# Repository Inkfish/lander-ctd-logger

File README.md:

# CTD Logger for the Inkfish Open Oceans Landers

This repository holds firmware for the [SparkFun OpenLog][] specifically tailored to logging measurements from the [Sea-Bird SBE 49 FastCAT CTD][SBE 49] on the Inkfish Open Oceans landers.

  [SBE 49]: https://www.seabird.com/sbe-49-fastcat-ctd/product?id=60762467704
  [SparkFun OpenLog]: https://www.sparkfun.com/products/13712

The SBE 49 is capable of sampling at 16 Hz, but the lander controller functions best when it receives CTD data at 1 Hz. This firmware logs at the higher rate, then downsamples the data and passes it to the controller at the lower rate.

## Hardware

### Custom PCB

**(NEW):** The `hardware` directory contains KiCad designs for a printed circuit board that accepts a wider input voltage range and is designed to be significantly more resilient to power surges.

### Breadboard

The only components needed are the [SparkFun OpenLog][] and a [MAX3232 transceiver breakout][MAX3232].

(Note that some components are represented as SIP ICs for purposes of illustration. The leftmost pin of the MAX3232 transceiver above is `T1OUT`.)

In summary, the circuit interposes the communication between the CTD and Lander Control Board:

    +-------+          +---------------+         +-----------+
    | CTD   |          | MAX3232       |         | OpenLog   |
    |       |          |               |         |           |
    |   TX -------------> R1IN  R1OUT ------------> RX       |
    |       |  RS-232  |               |   TTL   |           |
    |       |    +------- T1OUT  T1IN <------------ TX       |
    |       |    |     |               |         |           |
    +-------+    |     +---------------+         +-----------+
                 |
                 |     +-------------------------------------+
                 |     | LCB                                 |
                 |     |                                     |
                 +------> CTD_RX                             |
                       |                                     |
                       +-------------------------------------+

**Note:** Consider the need to attach the programmer to the OpenLog. See Programming section below.

  [MAX3232]: https://www.sparkfun.com/products/11189

## Compiling

This project uses [PlatformIO][]. You can build the firmware and program the OpenLog using the PlatformIO Core CLI tool.

  [PlatformIO]: https://platformio.org/

First, clone the repository with submodules:

    git submodule update --init

Patch `SerialPort.h` to disable `BUFFERED_TX` and `ENABLE_RX_ERROR_CHECKING`:

    sed -i.bak \
      -e 's/\(#define BUFFERED_TX\) 1/\1 0/' \
      -e 's/\(#define ENABLE_RX_ERROR_CHECKING\) 1/\1 0/' \
      Libraries/SerialPort/SerialPort/SerialPort.h

Compile the project using PlatformIO to check for errors:

    pio run

## Programming

The OpenLog can be programmed using a 4-wire TTL UART to USB adapter. Review the [OpenLog Hookup Guide][hookup] for details on wiring. Importantly, the OpenLog `DTR` pin (inexplicably labeled `GRN`) must be connected to the programmer's `DTR` or `RTS` output.

  [hookup]: https://learn.sparkfun.com/tutorials/openlog-hookup-guide#hardware-hookup

    pio run -t upload

### Programming with a RS-232 cable

A USB to RS-232 cable (DB-9 connector) can also be used for programming. The `RX`/`TX` pinout on the DB-9 connector must be confirmed due to the various permutations.

  | DB-9              | MAX3232           | OpenLog |
  | ----------------- | ----------------- | ------- |
  | `TX` (pin 2 or 3) | `R1IN` → `R1OUT`  | `RX`    |
  | `RX` (pin 2 or 3) | `T1OUT` ← `T1IN`  | `TX`    |
  | `DTR` (pin 4)     | `R2IN`  → `R2OUT` | `GRN`   |
  | `GND` (pin 5)     | `GND`             | `GND`   |

### Programming with a Bus Pirate

The [Bus Pirate][] can be used as a programmer. Attach the pins as follows:

  | Bus Pirate | OpenLog |
  | ---------- | ------- |
  | `MOSI`     | `RX`    |
  | `MISO`     | `TX`    |
  | `CLK`      | `GRN`   | 
  | `GND`      | `GND`   |

Place the Bus Pirate into the transparent UART bridge mode with flow control signaling:

    # Enter UART mode, use baud 115200 for programming
    HiZ>m
    2. UART
    (1)>2
    ...

    # Enable power output on the pins
    UART>W
    POWER SUPPLIES ON
    Clutch engaged!!!

    # Start the transparent bridge
    UART>(3)
    UART bridge
    Reset to exit
    Are you sure? y

Disconnect the terminal session and proceed with programming the board.

  [Bus Pirate]: http://dangerousprototypes.com/docs/Bus_Pirate

## Configuration

By default, the OpenLog expects to receive and transmit data at 9600 baud, the same rate as the Lander Control Board. If this needs to be changed, a different baud rate can be written to the file `config.txt` at the root of the microSD card.

The SBE 49 must be configured for `OUTPUTFORMAT=3`, engineering units in decimal. 

## Testing

A quick and dirty test script can be used to send fake samples to the logger from a PC. The script counts the number of downsampled replies that match expected values.

    python3 test/simctd.py --sal --sv /dev/tty.usbserial

The `--sal` and `--sv` flags simulate the `OUTPUTSAL` (salinity) and `OUTPUTSV` (sound velocity) options on the SBE 49.

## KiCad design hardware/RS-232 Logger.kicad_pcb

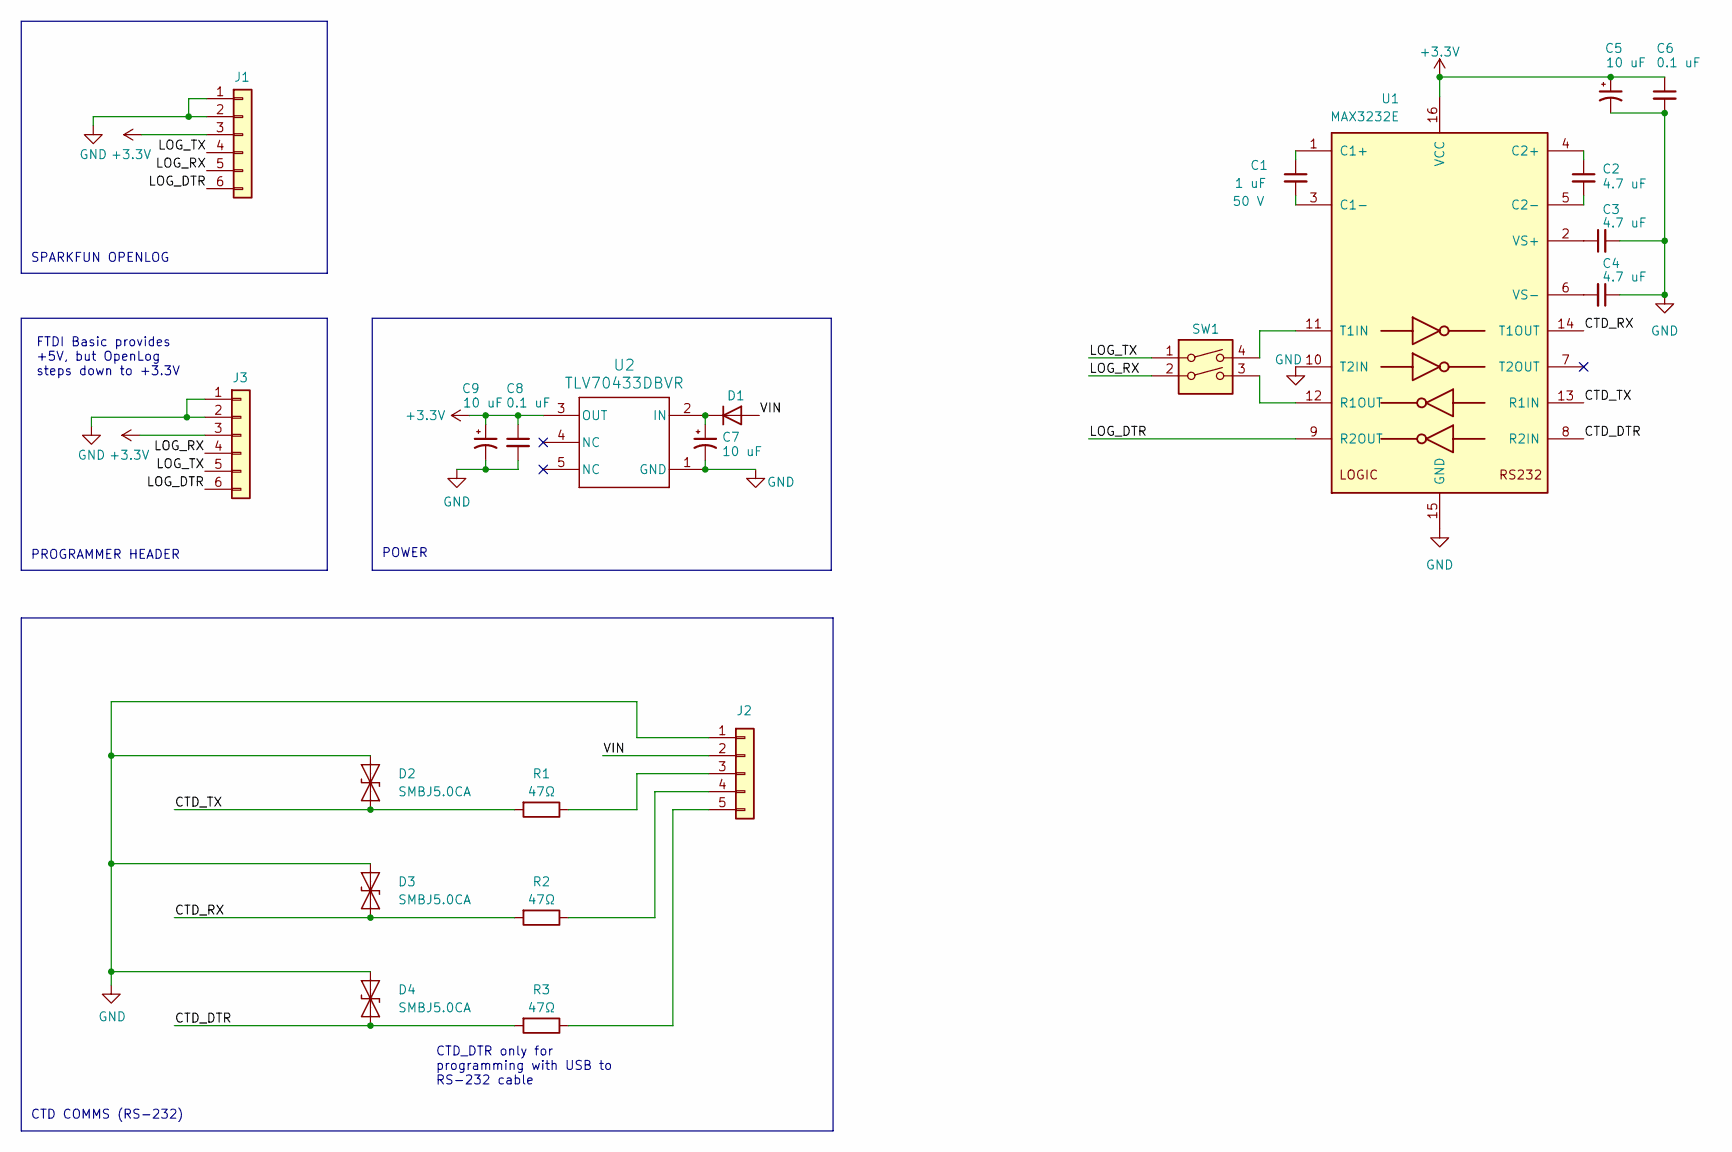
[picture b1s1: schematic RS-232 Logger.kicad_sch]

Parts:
C1: 1 uF; C_0805_2012Metric; Voltage 50 V; DigiKey CL21B105KBFNNNG
C2, C3, C4: 4.7 uF; C_0805_2012Metric; DigiKey CL21A475KBQNNNE
C5, C9: 10 uF; CAP_4 X 5.8_PAN; DigiKey EEE-FK1C100R
C6, C8: 0.1 uF; C_0805_2012Metric; DigiKey CL21B104KBCNNNC
C7: 10 uF; CAP_4 X 5.8_PAN
D1: D; DO-214BA_MCH
D2, D3, D4: SMBJ5.0CA; D_SMA
J1: Conn_01x06; PinSocket_1x06_P2.54mm_Vertical
J2: Conn_01x05; TerminalBlock_Phoenix_PT-1,5-5-3.5-H_1x05_P3.50mm_Horizontal
J3: Conn_01x06; PinHeader_1x06_P2.54mm_Vertical
R1, R2, R3: 47Ω; R_0603_1608Metric; DigiKey ESR03EZPJ470
SW1: SW_DIP_x02; SW_DIP_SPSTx02_Slide_6.7x6.64mm_W8.61mm_P2.54mm_LowProfile
U1: MAX3232E; 21-0056-E_90-0106-16L_MXM
U2: TLV70433DBVR; DBV0005A_N

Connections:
+3.3V: C5.1, C6.1, C8.1, C9.1, J1.3, J3.3, U1.16 (VCC), U2.3 (OUT)
/CTD_DTR: D4.2 (A2), R3.2, U1.8 (R2IN)
/CTD_RX: D3.2 (A2), R2.2, U1.14 (T1OUT)
/CTD_TX: D2.2 (A2), R1.2, U1.13 (R1IN)
/LOG_DTR: J1.6, J3.6, U1.9 (R2OUT)
/LOG_RX: J1.5, J3.4, SW1.2
/LOG_TX: J1.4, J3.5, SW1.1
/VIN: D1.2 (A), J2.2
GND: C3.2, C4.1, C5.2, C6.2, C7.2, C8.2, C9.2, D2.1 (A1), D3.1 (A1), D4.1 (A1), J1.1, J1.2, J2.1, J3.1, J3.2, U1.10 (T2IN), U1.15 (GND), U2.1 (GND)
unnamed: C7.1, D1.1 (K), U2.2 (IN)
unnamed: J2.3, R1.1
unnamed: J2.4, R2.1
unnamed: J2.5, R3.1
unnamed: C1.1, U1.1 (C1+)
unnamed: C1.2, U1.3 (C1-)
unnamed: C2.1, U1.4 (C2+)
unnamed: C2.2, U1.5 (C2-)
unnamed: SW1.3, U1.12 (R1OUT)
unnamed: SW1.4, U1.11 (T1IN)
unnamed: C3.1, U1.2 (VS+)
unnamed: C4.2, U1.6 (VS-)

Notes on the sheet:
CTD_DTR only for programming with USB to RS-232 cable
FTDI Basic provides +5V, but OpenLog steps down to +3.3V
CTD COMMS (RS-232)
SPARKFUN OPENLOG
POWER
PROGRAMMER HEADER

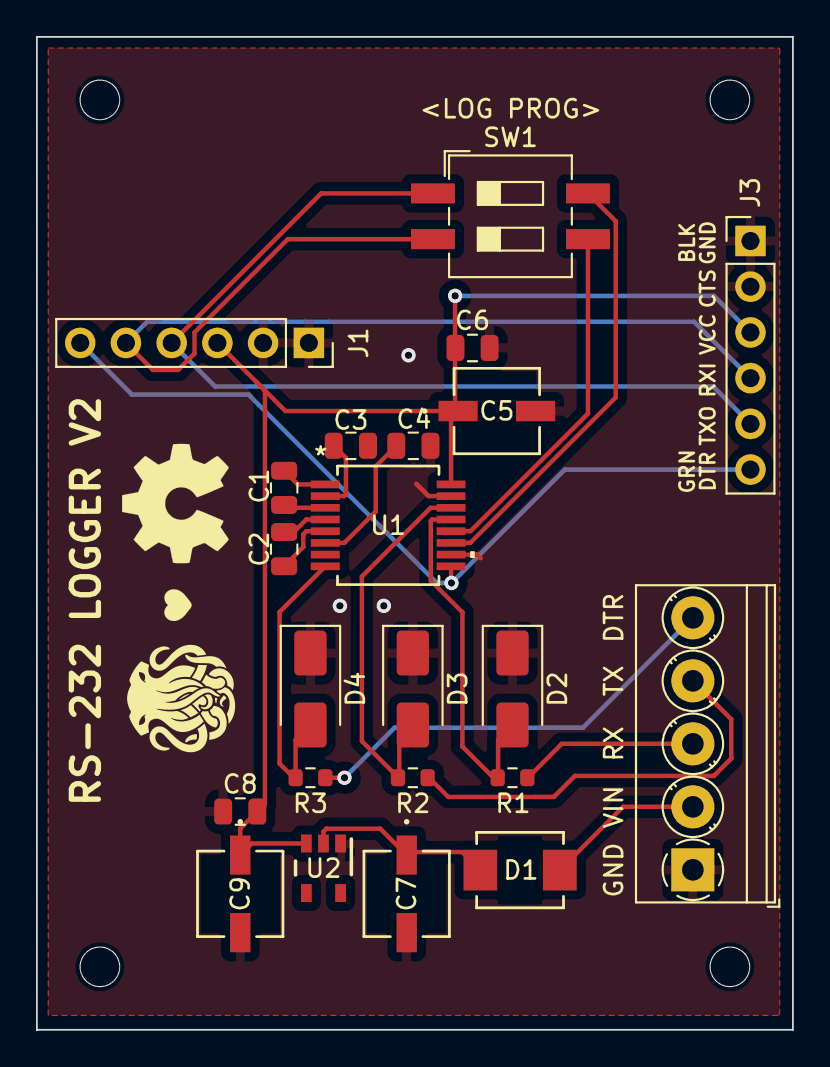
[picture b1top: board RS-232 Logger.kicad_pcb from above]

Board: 2 copper layers, 42.0 x 55.2 mm, 22 parts (0 on the bottom side), 21 nets.

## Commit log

2023-07-30 Remove unnecessary files
2023-07-30 Use PlatformIO to build
2023-07-30 Add SdFat and SerialPort as submodules
2023-08-06 Silence debug output on TX pin
2023-08-07 Remove unused settings
2023-08-07 General code housekeeping
2023-08-07 Improve SVG for browser rendering
2023-08-07 Tweak wires to improve clarity
2023-08-07 Add more wiring information
2023-08-07 Set baudrate only once
2023-08-07 Initial README
2023-08-07 Downsample and emit CTD readings
2023-08-07 Lower receive buffer size
2023-08-07 Use dtostrf to build the output string
    Apparently Arduino's printf() cannot handle %f specifiers.
2023-08-07 Skip spaces between fields
2023-08-07 Use a ring buffer for input
2023-08-08 Optionally parse salinity and sound velocity
2023-08-08 Update README with programming instructions
2023-08-09 Add a note about the CTD output format
2023-08-09 Add a CTD simulator for testing
2023-08-09 Add RS-232 programming instructions
2023-08-13 Fix label on schematic
2024-01-10 Fix test condition to check expected length
2024-01-10 Use 3.3V power input
    The OpenLog features a voltage regulator that steps input power down to 3.3V.
    According to the ATmega328P data sheet (section 28, Electrical Characteristics),
    the maximum voltage on any pin is VCC + 0.5 = 3.8V.
    The SP3232E transceiver's voltage level on RxOUT = VCC + 0.3. Therefore the
    transceiver's VCC cannot exceed 3.5V or it will be out of spec with the ATmega.
2024-01-10 Add RS-232 Logger PCB design files
2024-01-10 Update diagram with new Fritzing part
